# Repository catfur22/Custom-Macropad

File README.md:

# Custom-Macropad
This is a custom macropad that i am making to make navigating in fusion 360 easier in terms of just needing the keyboard and the macropad for most basic stuff. I am building this because I like having my mouse available to do actual drawing and design instead of having to change camera placement and stuff and I feel like I could get things done quicker. Another reason im building this is that I think that this is a cool project topic and I also just want to make something and there is a tutorial. I also wanted it to solve a problem so thats how I got the idea to make it control fusion 360. The code hasn't ever been tested but it is there and I will make the code better once I build the actual project.

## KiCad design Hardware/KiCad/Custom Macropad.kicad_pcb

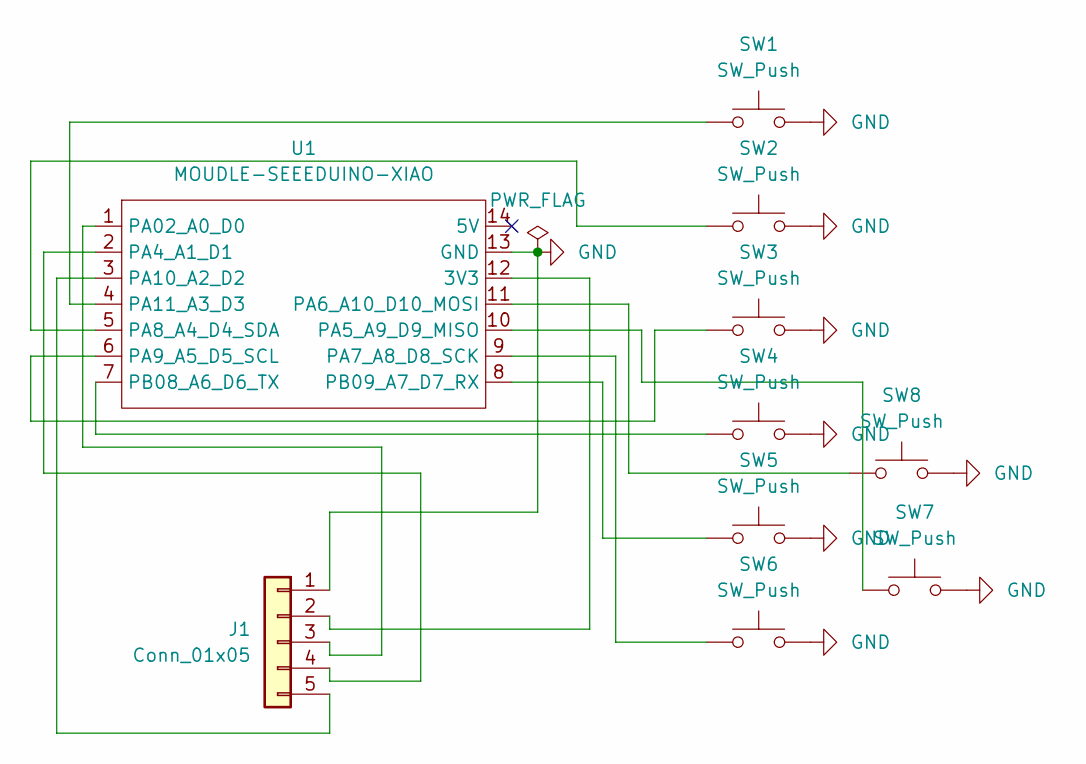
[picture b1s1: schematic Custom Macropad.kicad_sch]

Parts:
J1: Conn_01x05; PinSocket_1x05_P2.54mm_Horizontal
SW1, SW2, SW3, SW4, SW5, SW6, SW7, SW8: SW_Push; SW_Cherry_MX_1.00u_PCB
U1: MOUDLE-SEEEDUINO-XIAO; XIAO-Generic-Hybrid-14P-2.54-21X17.8MM

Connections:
GND: J1.1, SW1.2, SW2.2, SW3.2, SW4.2, SW5.2, SW6.2, SW7.2, SW8.2, U1.13 (GND)
unnamed: J1.2, U1.12 (3V3)
unnamed: J1.3, U1.1 (PA02_A0_D0)
unnamed: J1.4, U1.2 (PA4_A1_D1)
unnamed: J1.5, U1.3 (PA10_A2_D2)
unnamed: SW7.1, U1.10 (PA5_A9_D9_MISO)
unnamed: SW8.1, U1.11 (PA6_A10_D10_MOSI)
unnamed: SW6.1, U1.9 (PA7_A8_D8_SCK)
unnamed: SW2.1, U1.5 (PA8_A4_D4_SDA)
unnamed: SW3.1, U1.6 (PA9_A5_D5_SCL)
unnamed: SW1.1, U1.4 (PA11_A3_D3)
unnamed: SW4.1, U1.7 (PB08_A6_D6_TX)
unnamed: SW5.1, U1.8 (PB09_A7_D7_RX)

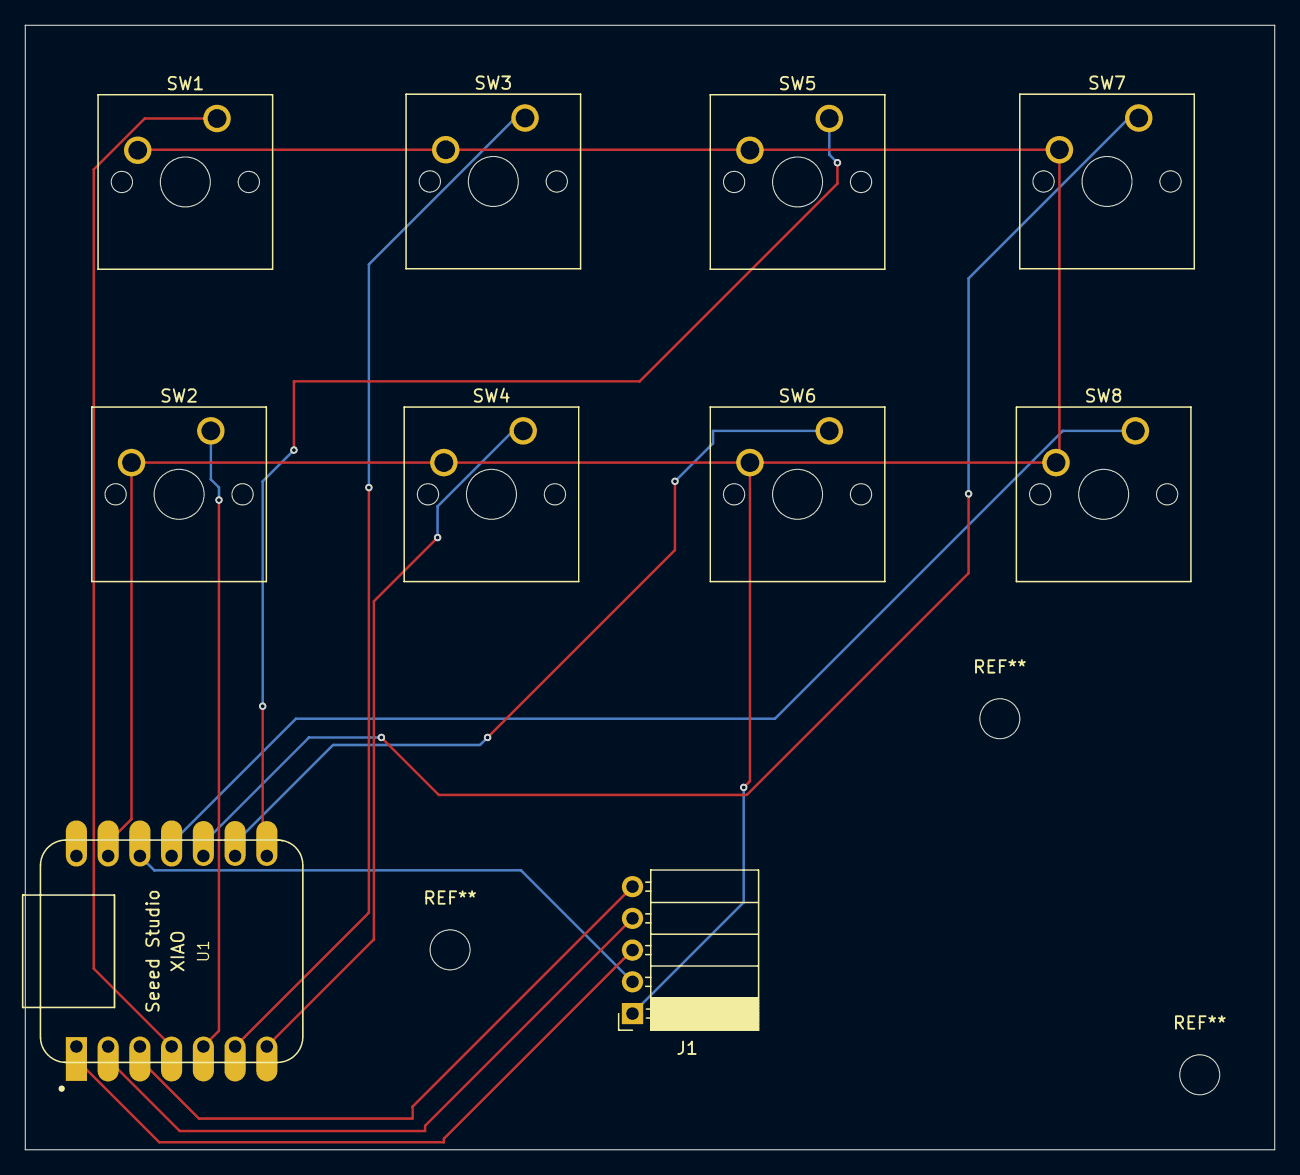
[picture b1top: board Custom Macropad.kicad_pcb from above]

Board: 2 copper layers, 100.0 x 90.0 mm, 10 parts (0 on the bottom side), 13 nets.
